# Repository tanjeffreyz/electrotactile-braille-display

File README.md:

<h1 align="center">Electrotactile Braille Display</h1> 

The Electrotactile Braille Display (ETBD) is a refreshable braille display that uses electrical pulses to simulate the feeling of braille dots on the user's fingertips. 
Because it has no moving parts, the ETBD has the potential to be much lighter, thinner, and cheaper compared to mechanical braille displays, which use physical braille pins.
 
<div align="center">
  
</div>
<br>
<div align="center">
  <a href="https://tanjeffreyz.github.io/electrotactile-braille-display"><b>Click here to view this project's full description</b></a>
</div>

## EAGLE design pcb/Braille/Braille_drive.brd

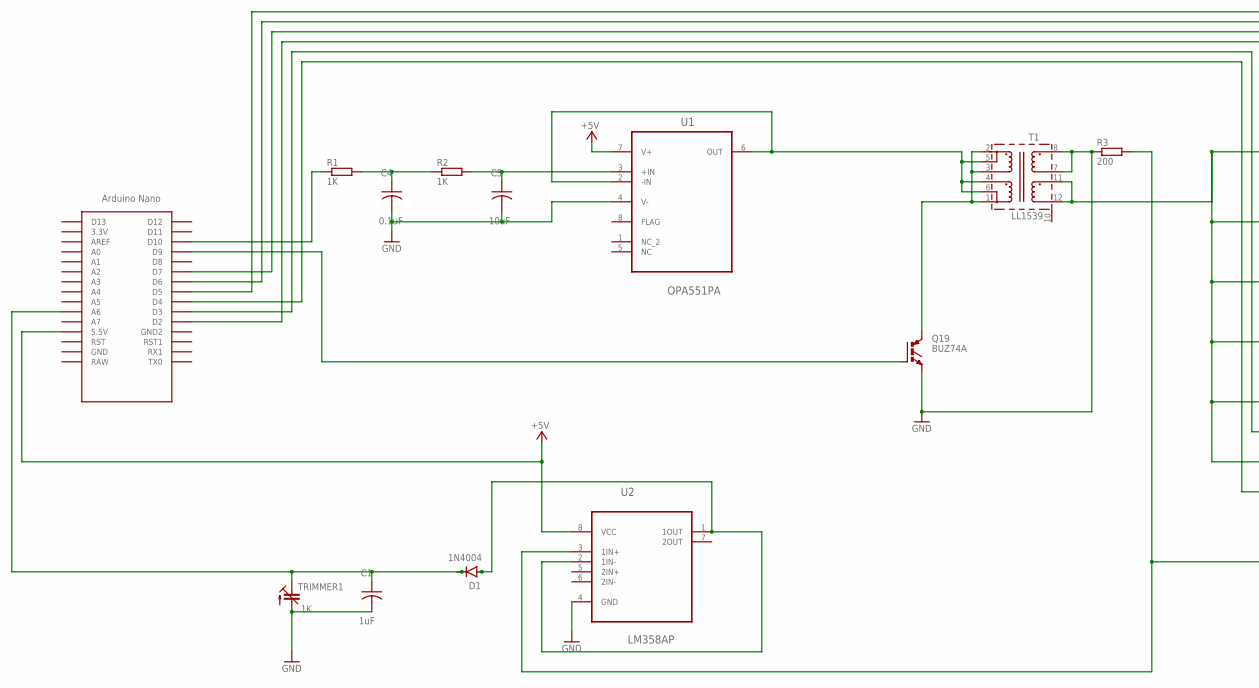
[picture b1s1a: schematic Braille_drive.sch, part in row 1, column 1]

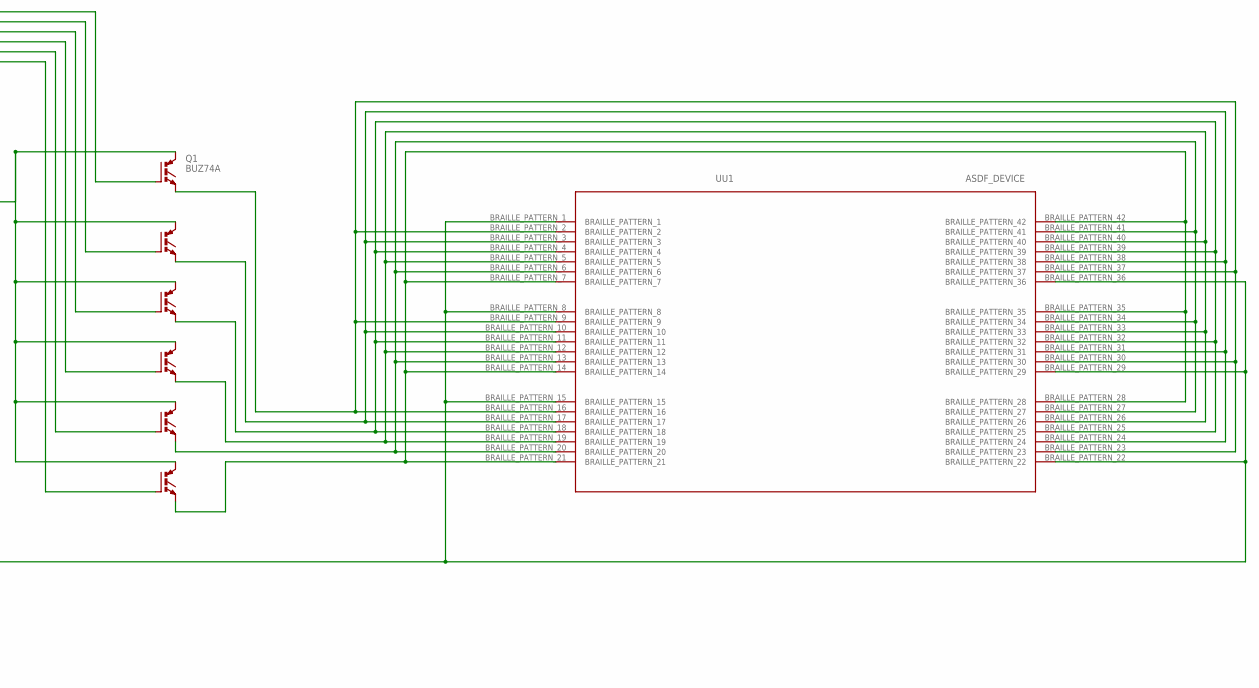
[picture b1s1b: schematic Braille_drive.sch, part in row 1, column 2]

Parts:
C1: 1uF; CAP_RADIAL_2MM
C4: 0.1uF; CAP_RADIAL_2MM
C5: 10uF; CAP_RADIAL_2MM
D1: 1N4004; DO-41
Q1, Q2, Q3, Q4, Q5, Q6, Q19: BUZ74A; TO220AV
R1, R2: 1K; 0204V
R3: 200; 0204V
T1: LL1539
TRIMMER1: 1K; CTRIM3040.452
U1: OPA551PA; DIP254P762X508-8
U2: LM358AP; DIP254P762X508-8
U$1: NANO
UU1: ASDF_DEVICE; BRAILLE_PATTERN1

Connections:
+5V: U1.7 (V+), U2.8 (VCC), U$1.5V (5.5V)
GND: C1.2, C4.2, C5.2, Q19.E, R3.1, T1.7, T1.8, TRIMMER1.2 (A), U1.4 (V-), U2.4 (GND)
unnamed: R1.1, U$1.D10
unnamed: C4.1, R1.2, R2.1
unnamed: C5.1, R2.2, U1.3 (+IN)
unnamed: T1.4, T1.5, T1.6, U1.2 (-IN), U1.6 (OUT)
unnamed: Q19.C, T1.1, T1.2, T1.3
unnamed: Q19.G, U$1.D9
unnamed: D1.A, U2.1 (1OUT), U2.2 (1IN-)
unnamed: C1.1, D1.C, TRIMMER1.1A (E), U$1.A6
unnamed: Q6.G, U$1.D4
unnamed: Q5.G, U$1.D3
unnamed: Q1.C, Q2.C, Q3.C, Q4.C, Q5.C, Q6.C, T1.11, T1.12
unnamed: Q4.G, U$1.D2
unnamed: Q6.E, UU1.BRAILLE_PATTERN_7, UU1.BRAILLE_PATTERN_14, UU1.BRAILLE_PATTERN_21, UU1.BRAILLE_PATTERN_28, UU1.BRAILLE_PATTERN_35, UU1.BRAILLE_PATTERN_42
unnamed: Q3.G, U$1.D7
unnamed: Q2.G, U$1.D6
unnamed: Q1.G, U$1.D5
unnamed: R3.2, U2.3 (1IN+), UU1.BRAILLE_PATTERN_1, UU1.BRAILLE_PATTERN_8, UU1.BRAILLE_PATTERN_15, UU1.BRAILLE_PATTERN_22, UU1.BRAILLE_PATTERN_29, UU1.BRAILLE_PATTERN_36
unnamed: Q5.E, UU1.BRAILLE_PATTERN_6, UU1.BRAILLE_PATTERN_13, UU1.BRAILLE_PATTERN_20, UU1.BRAILLE_PATTERN_27, UU1.BRAILLE_PATTERN_34, UU1.BRAILLE_PATTERN_41
unnamed: Q1.E, UU1.BRAILLE_PATTERN_2, UU1.BRAILLE_PATTERN_9, UU1.BRAILLE_PATTERN_16, UU1.BRAILLE_PATTERN_23, UU1.BRAILLE_PATTERN_30, UU1.BRAILLE_PATTERN_37
unnamed: Q4.E, UU1.BRAILLE_PATTERN_5, UU1.BRAILLE_PATTERN_12, UU1.BRAILLE_PATTERN_19, UU1.BRAILLE_PATTERN_26, UU1.BRAILLE_PATTERN_33, UU1.BRAILLE_PATTERN_40
unnamed: Q3.E, UU1.BRAILLE_PATTERN_4, UU1.BRAILLE_PATTERN_11, UU1.BRAILLE_PATTERN_18, UU1.BRAILLE_PATTERN_25, UU1.BRAILLE_PATTERN_32, UU1.BRAILLE_PATTERN_39
unnamed: Q2.E, UU1.BRAILLE_PATTERN_3, UU1.BRAILLE_PATTERN_10, UU1.BRAILLE_PATTERN_17, UU1.BRAILLE_PATTERN_24, UU1.BRAILLE_PATTERN_31, UU1.BRAILLE_PATTERN_38

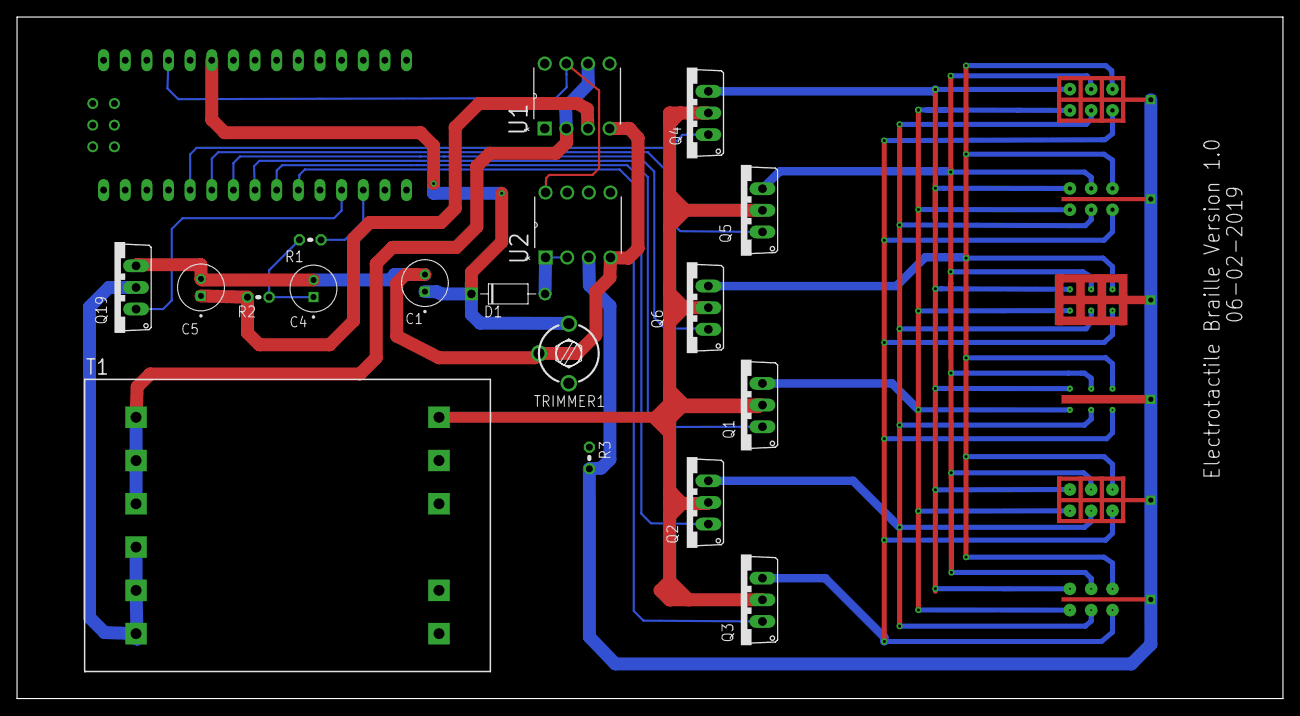
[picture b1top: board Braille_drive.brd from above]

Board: 2 copper layers, 148.6 x 80.0 mm, 20 parts (0 on the bottom side), 24 nets.

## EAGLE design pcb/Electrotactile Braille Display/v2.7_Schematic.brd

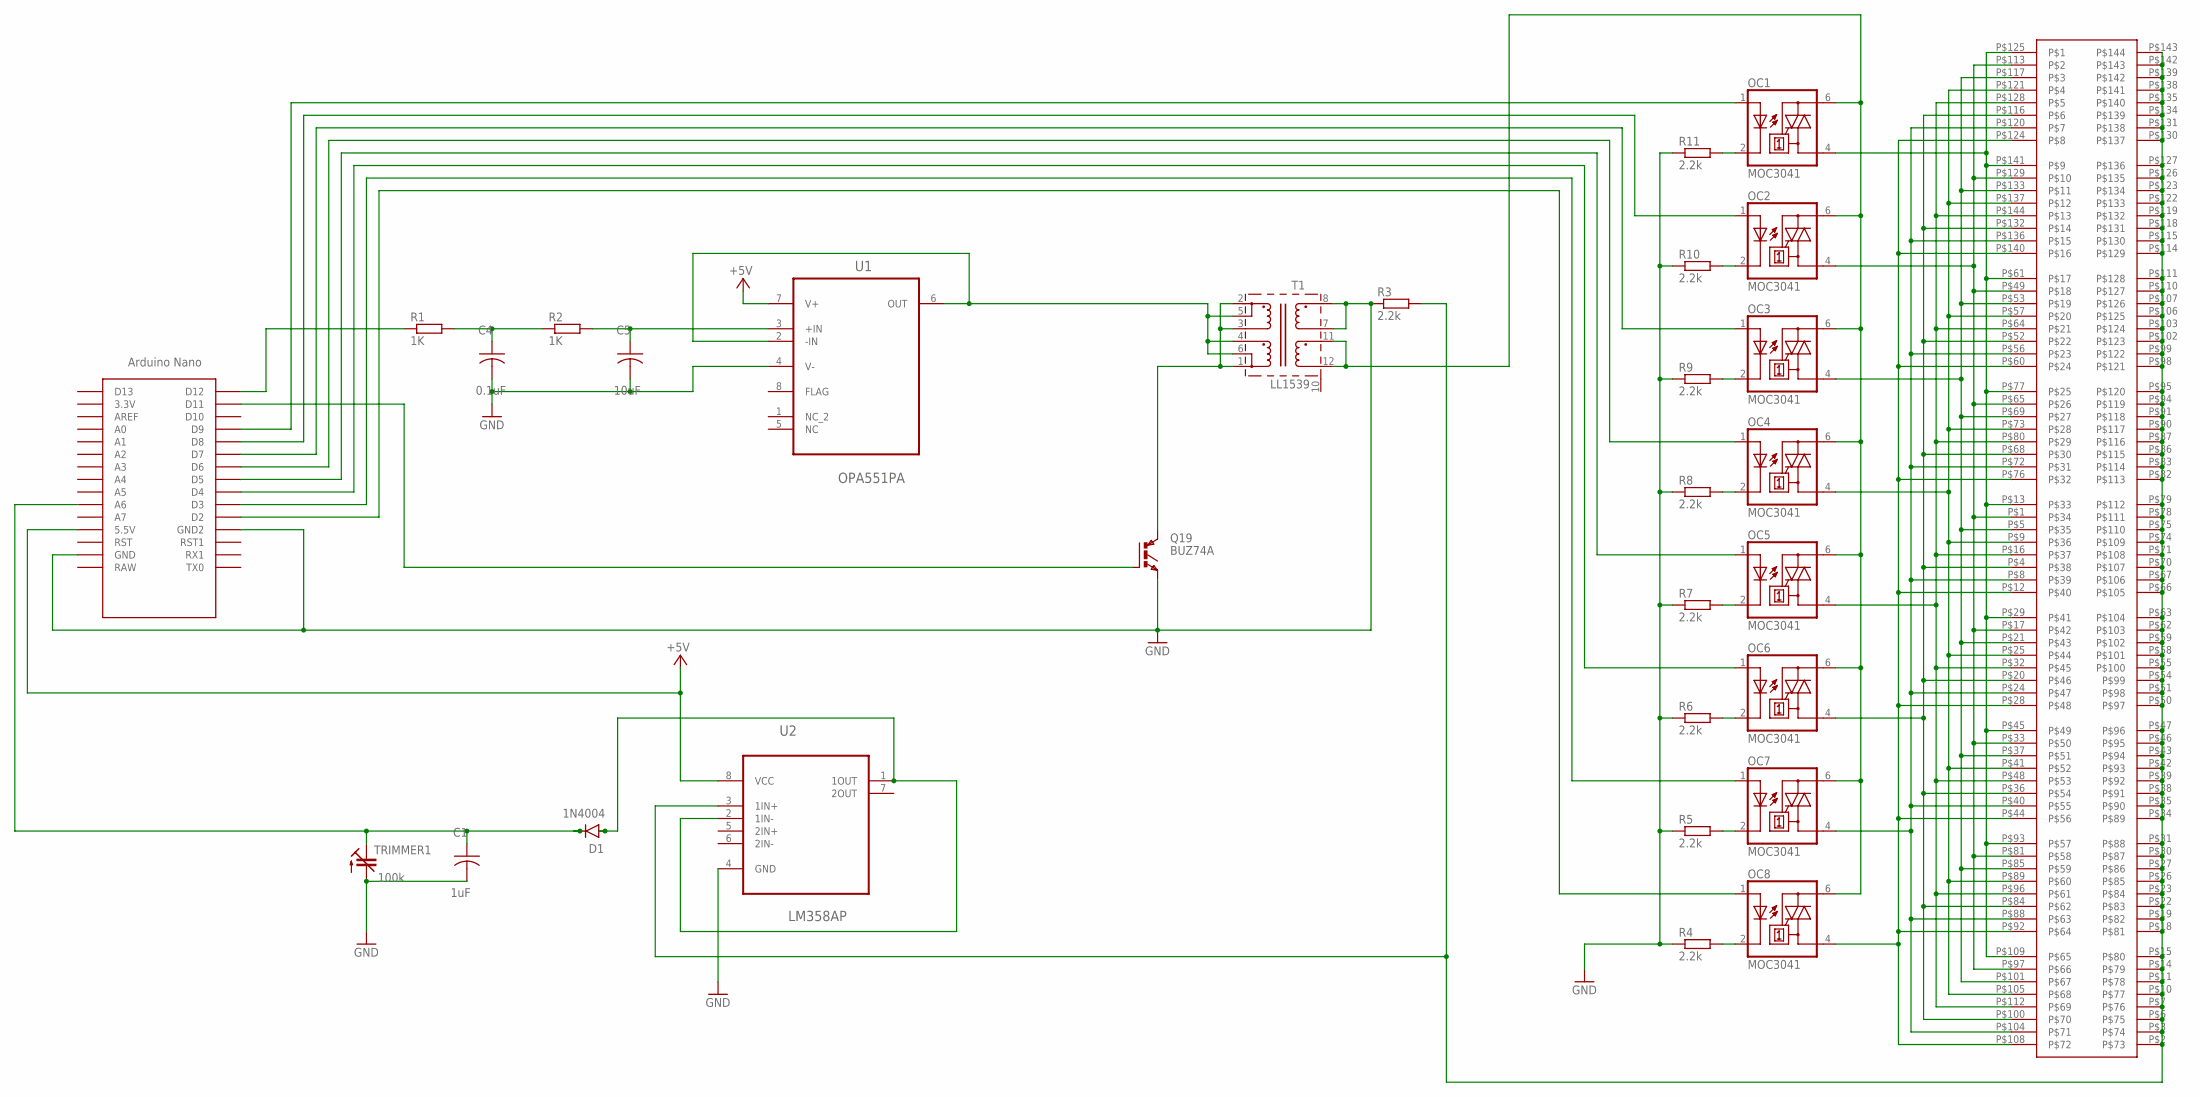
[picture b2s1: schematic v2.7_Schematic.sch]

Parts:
C1: 1uF; CAP_RADIAL_2MM
C4: 0.1uF; CAP_RADIAL_2MM
C5: 10uF; CAP_RADIAL_2MM
D1: 1N4004; DO-41
OC1, OC2, OC3, OC4, OC5, OC6, OC7, OC8: MOC3041; DIL06
Q19: BUZ74A; TO220AV
R1, R2: 1K; 0204V
R3, R4, R5, R6, R7, R8, R9, R10, R11: 2.2k; 0204V
T1: LL1539
TRIMMER1: 100k; CTRIM3040.452
U1: OPA551PA; DIP254P762X508-8
U2: LM358AP; DIP254P762X508-8
U$1: NANO
U$2: DOTS_V2

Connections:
+5V: U1.7 (V+), U2.8 (VCC), U$1.5V (5.5V)
GND: C1.2, C4.2, C5.2, Q19.E, R3.1, R4.1, R5.1, R6.1, R7.1, R8.1, R9.1, R10.1, R11.1, T1.7, T1.8, TRIMMER1.2 (A), U1.4 (V-), U2.4 (GND), U$1.GND, U$1.GND1 (GND2)
unnamed: OC7.2 (C), R5.2
unnamed: C4.1, R1.2, R2.1
unnamed: C5.1, R2.2, U1.3 (+IN)
unnamed: T1.4, T1.5, T1.6, U1.2 (-IN), U1.6 (OUT)
unnamed: Q19.C, T1.1, T1.2, T1.3
unnamed: Q19.G, U$1.D11
unnamed: D1.A, U2.1 (1OUT), U2.2 (1IN-)
unnamed: C1.1, D1.C, TRIMMER1.1A (E), U$1.A6
unnamed: OC8.1 (A), U$1.D2
unnamed: OC7.1 (A), U$1.D3
unnamed: OC2.1 (A), U$1.D8
unnamed: OC6.1 (A), U$1.D4
unnamed: R1.1, U$1.D12
unnamed: OC5.1 (A), U$1.D5
unnamed: OC4.1 (A), U$1.D6
unnamed: OC3.1 (A), U$1.D7
unnamed: R3.2, U2.3 (1IN+), U$2.P$2, U$2.P$3, U$2.P$6, U$2.P$7, U$2.P$10, U$2.P$11, U$2.P$14, U$2.P$15, U$2.P$18, U$2.P$19, U$2.P$22, U$2.P$23, U$2.P$26, U$2.P$27, U$2.P$30, U$2.P$31, U$2.P$34, U$2.P$35, U$2.P$38, U$2.P$39, U$2.P$42, U$2.P$43, U$2.P$46, U$2.P$47, U$2.P$50, U$2.P$51, U$2.P$54, U$2.P$55, U$2.P$58, U$2.P$59, U$2.P$62, U$2.P$63, U$2.P$66, U$2.P$67, U$2.P$70, U$2.P$71, U$2.P$74, U$2.P$75, U$2.P$78, U$2.P$79, U$2.P$82, U$2.P$83, U$2.P$86, U$2.P$87, U$2.P$90, U$2.P$91, U$2.P$94, U$2.P$95, U$2.P$98, U$2.P$99, U$2.P$102, U$2.P$103, U$2.P$106, U$2.P$107, U$2.P$110, U$2.P$111, U$2.P$114, U$2.P$115, U$2.P$118, U$2.P$119, U$2.P$122, U$2.P$123, U$2.P$126, U$2.P$127, U$2.P$130, U$2.P$131, U$2.P$134, U$2.P$135, U$2.P$138, U$2.P$139, U$2.P$142, U$2.P$143
unnamed: OC1.6 (A2), OC2.6 (A2), OC3.6 (A2), OC4.6 (A2), OC5.6 (A2), OC6.6 (A2), OC7.6 (A2), OC8.6 (A2), T1.11, T1.12
unnamed: OC4.4 (A1), U$2.P$9, U$2.P$25, U$2.P$41, U$2.P$57, U$2.P$73, U$2.P$89, U$2.P$105, U$2.P$121, U$2.P$137
unnamed: OC1.1 (A), U$1.D9
unnamed: OC2.4 (A1), U$2.P$1, U$2.P$17, U$2.P$33, U$2.P$49, U$2.P$65, U$2.P$81, U$2.P$97, U$2.P$113, U$2.P$129
unnamed: OC3.4 (A1), U$2.P$5, U$2.P$21, U$2.P$37, U$2.P$53, U$2.P$69, U$2.P$85, U$2.P$101, U$2.P$117, U$2.P$133
unnamed: OC5.4 (A1), U$2.P$16, U$2.P$32, U$2.P$48, U$2.P$64, U$2.P$80, U$2.P$96, U$2.P$112, U$2.P$128, U$2.P$144
unnamed: OC6.4 (A1), U$2.P$4, U$2.P$20, U$2.P$36, U$2.P$52, U$2.P$68, U$2.P$84, U$2.P$100, U$2.P$116, U$2.P$132
unnamed: OC7.4 (A1), U$2.P$8, U$2.P$24, U$2.P$40, U$2.P$56, U$2.P$72, U$2.P$88, U$2.P$104, U$2.P$120, U$2.P$136
unnamed: OC8.4 (A1), U$2.P$12, U$2.P$28, U$2.P$44, U$2.P$60, U$2.P$76, U$2.P$92, U$2.P$108, U$2.P$124, U$2.P$140
unnamed: OC8.2 (C), R4.2
unnamed: OC1.4 (A1), U$2.P$13, U$2.P$29, U$2.P$45, U$2.P$61, U$2.P$77, U$2.P$93, U$2.P$109, U$2.P$125, U$2.P$141
unnamed: OC6.2 (C), R6.2
unnamed: OC5.2 (C), R7.2
unnamed: OC4.2 (C), R8.2
unnamed: OC3.2 (C), R9.2
unnamed: OC2.2 (C), R10.2
unnamed: OC1.2 (C), R11.2

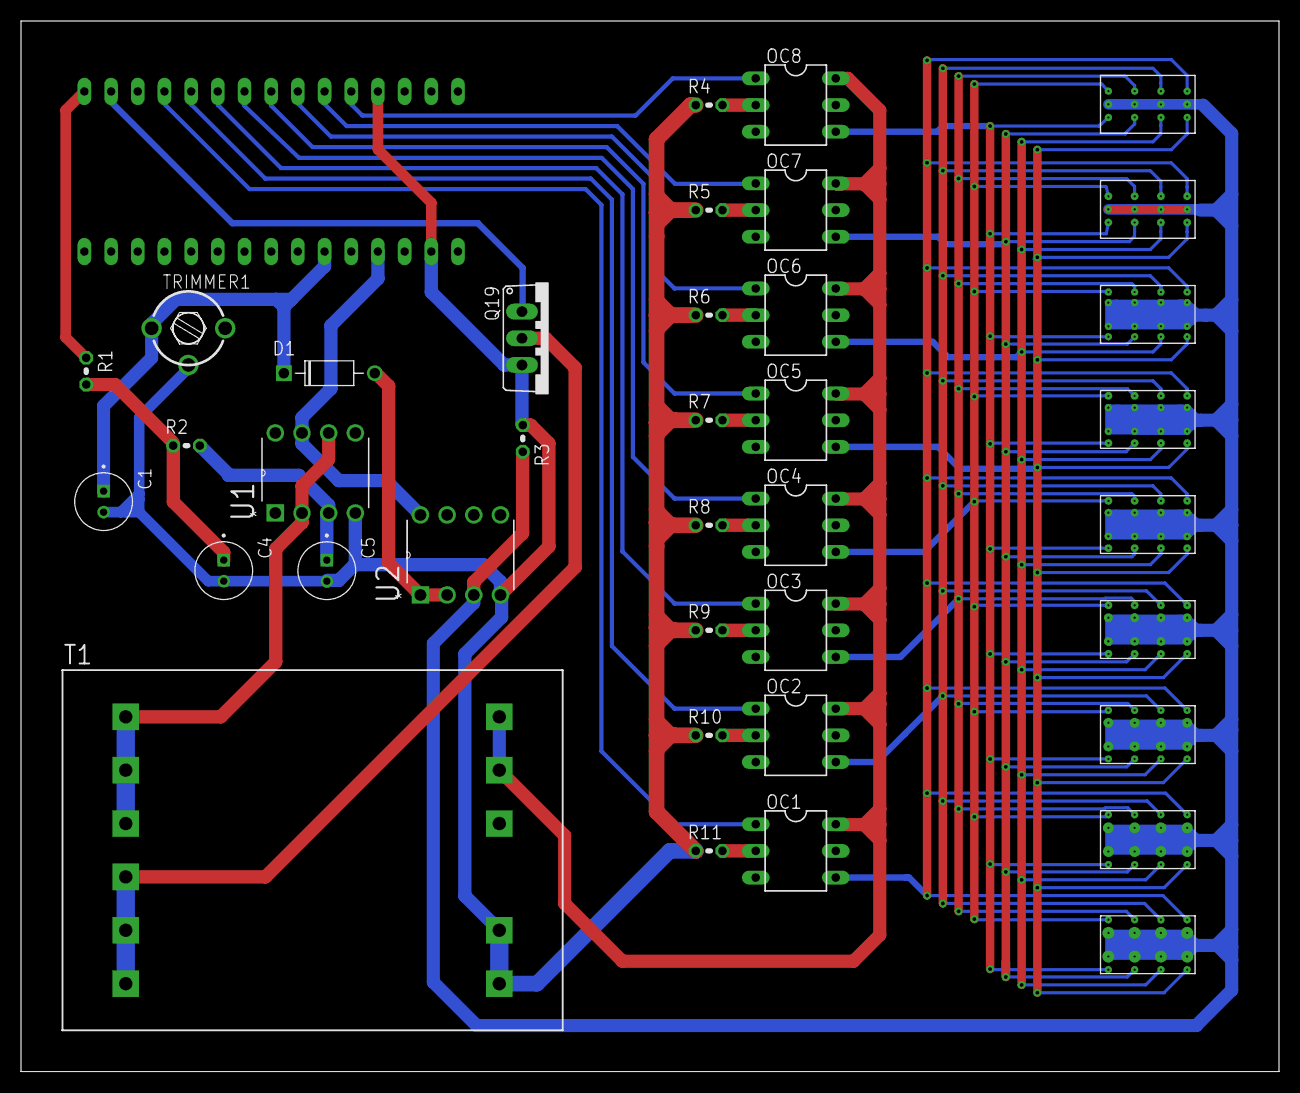
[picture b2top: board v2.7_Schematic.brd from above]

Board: 2 copper layers, 119.8 x 100.0 mm, 30 parts (0 on the bottom side), 36 nets.

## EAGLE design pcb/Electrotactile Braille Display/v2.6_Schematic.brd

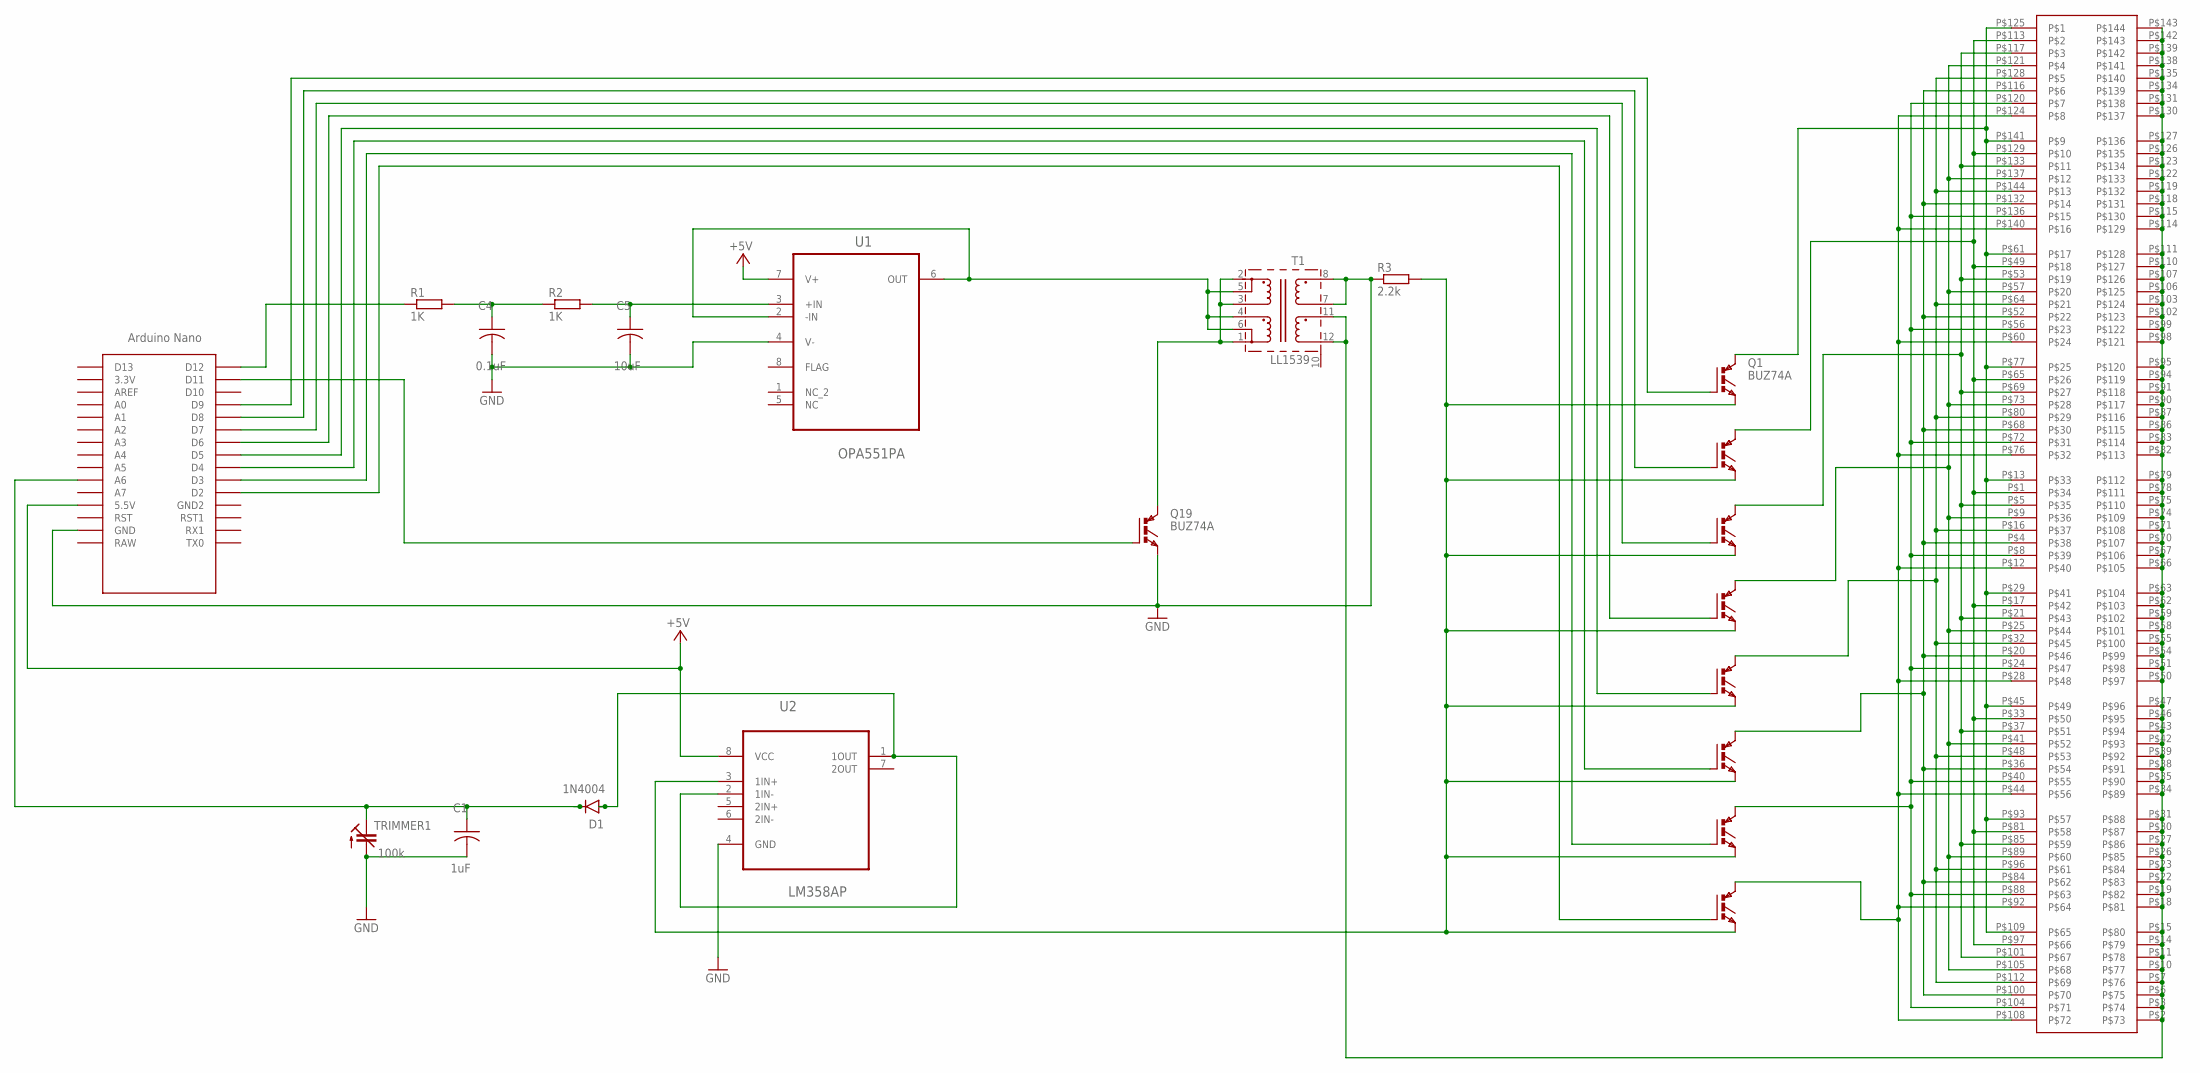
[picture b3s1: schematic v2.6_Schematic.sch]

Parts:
C1: 1uF; CAP_RADIAL_2MM
C4: 0.1uF; CAP_RADIAL_2MM
C5: 10uF; CAP_RADIAL_2MM
D1: 1N4004; DO-41
Q1, Q2, Q3, Q4, Q5, Q6, Q7, Q8, Q19: BUZ74A; TO220AV
R1, R2: 1K; 0204V
R3: 2.2k; 0204V
T1: LL1539
TRIMMER1: 100k; CTRIM3040.452
U1: OPA551PA; DIP254P762X508-8
U2: LM358AP; DIP254P762X508-8
U$1: NANO
U$2: DOTS_V2

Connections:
+5V: U1.7 (V+), U2.8 (VCC), U$1.5V (5.5V)
GND: C1.2, C4.2, C5.2, Q19.E, R3.1, T1.7, T1.8, TRIMMER1.2 (A), U1.4 (V-), U2.4 (GND), U$1.GND
unnamed: T1.11, T1.12, U$2.P$2, U$2.P$3, U$2.P$6, U$2.P$7, U$2.P$10, U$2.P$11, U$2.P$14, U$2.P$15, U$2.P$18, U$2.P$19, U$2.P$22, U$2.P$23, U$2.P$26, U$2.P$27, U$2.P$30, U$2.P$31, U$2.P$34, U$2.P$35, U$2.P$38, U$2.P$39, U$2.P$42, U$2.P$43, U$2.P$46, U$2.P$47, U$2.P$50, U$2.P$51, U$2.P$54, U$2.P$55, U$2.P$58, U$2.P$59, U$2.P$62, U$2.P$63, U$2.P$66, U$2.P$67, U$2.P$70, U$2.P$71, U$2.P$74, U$2.P$75, U$2.P$78, U$2.P$79, U$2.P$82, U$2.P$83, U$2.P$86, U$2.P$87, U$2.P$90, U$2.P$91, U$2.P$94, U$2.P$95, U$2.P$98, U$2.P$99, U$2.P$102, U$2.P$103, U$2.P$106, U$2.P$107, U$2.P$110, U$2.P$111, U$2.P$114, U$2.P$115, U$2.P$118, U$2.P$119, U$2.P$122, U$2.P$123, U$2.P$126, U$2.P$127, U$2.P$130, U$2.P$131, U$2.P$134, U$2.P$135, U$2.P$138, U$2.P$139, U$2.P$142, U$2.P$143
unnamed: C4.1, R1.2, R2.1
unnamed: C5.1, R2.2, U1.3 (+IN)
unnamed: T1.4, T1.5, T1.6, U1.2 (-IN), U1.6 (OUT)
unnamed: Q19.C, T1.1, T1.2, T1.3
unnamed: Q19.G, U$1.D11
unnamed: D1.A, U2.1 (1OUT), U2.2 (1IN-)
unnamed: C1.1, D1.C, TRIMMER1.1A (E), U$1.A6
unnamed: Q8.G, U$1.D2
unnamed: Q7.G, U$1.D3
unnamed: Q2.G, U$1.D8
unnamed: Q6.G, U$1.D4
unnamed: R1.1, U$1.D12
unnamed: Q5.G, U$1.D5
unnamed: Q4.G, U$1.D6
unnamed: Q3.G, U$1.D7
unnamed: Q1.E, Q2.E, Q3.E, Q4.E, Q5.E, Q6.E, Q7.E, Q8.E, R3.2, U2.3 (1IN+)
unnamed: Q4.C, U$2.P$9, U$2.P$25, U$2.P$41, U$2.P$57, U$2.P$73, U$2.P$89, U$2.P$105, U$2.P$121, U$2.P$137
unnamed: Q1.G, U$1.D9
unnamed: Q2.C, U$2.P$1, U$2.P$17, U$2.P$33, U$2.P$49, U$2.P$65, U$2.P$81, U$2.P$97, U$2.P$113, U$2.P$129
unnamed: Q3.C, U$2.P$5, U$2.P$21, U$2.P$37, U$2.P$53, U$2.P$69, U$2.P$85, U$2.P$101, U$2.P$117, U$2.P$133
unnamed: Q5.C, U$2.P$16, U$2.P$32, U$2.P$48, U$2.P$64, U$2.P$80, U$2.P$96, U$2.P$112, U$2.P$128, U$2.P$144
unnamed: Q6.C, U$2.P$4, U$2.P$20, U$2.P$36, U$2.P$52, U$2.P$68, U$2.P$84, U$2.P$100, U$2.P$116, U$2.P$132
unnamed: Q7.C, U$2.P$8, U$2.P$24, U$2.P$40, U$2.P$56, U$2.P$72, U$2.P$88, U$2.P$104, U$2.P$120, U$2.P$136
unnamed: Q8.C, U$2.P$12, U$2.P$28, U$2.P$44, U$2.P$60, U$2.P$76, U$2.P$92, U$2.P$108, U$2.P$124, U$2.P$140
unnamed: Q1.C, U$2.P$13, U$2.P$29, U$2.P$45, U$2.P$61, U$2.P$77, U$2.P$93, U$2.P$109, U$2.P$125, U$2.P$141

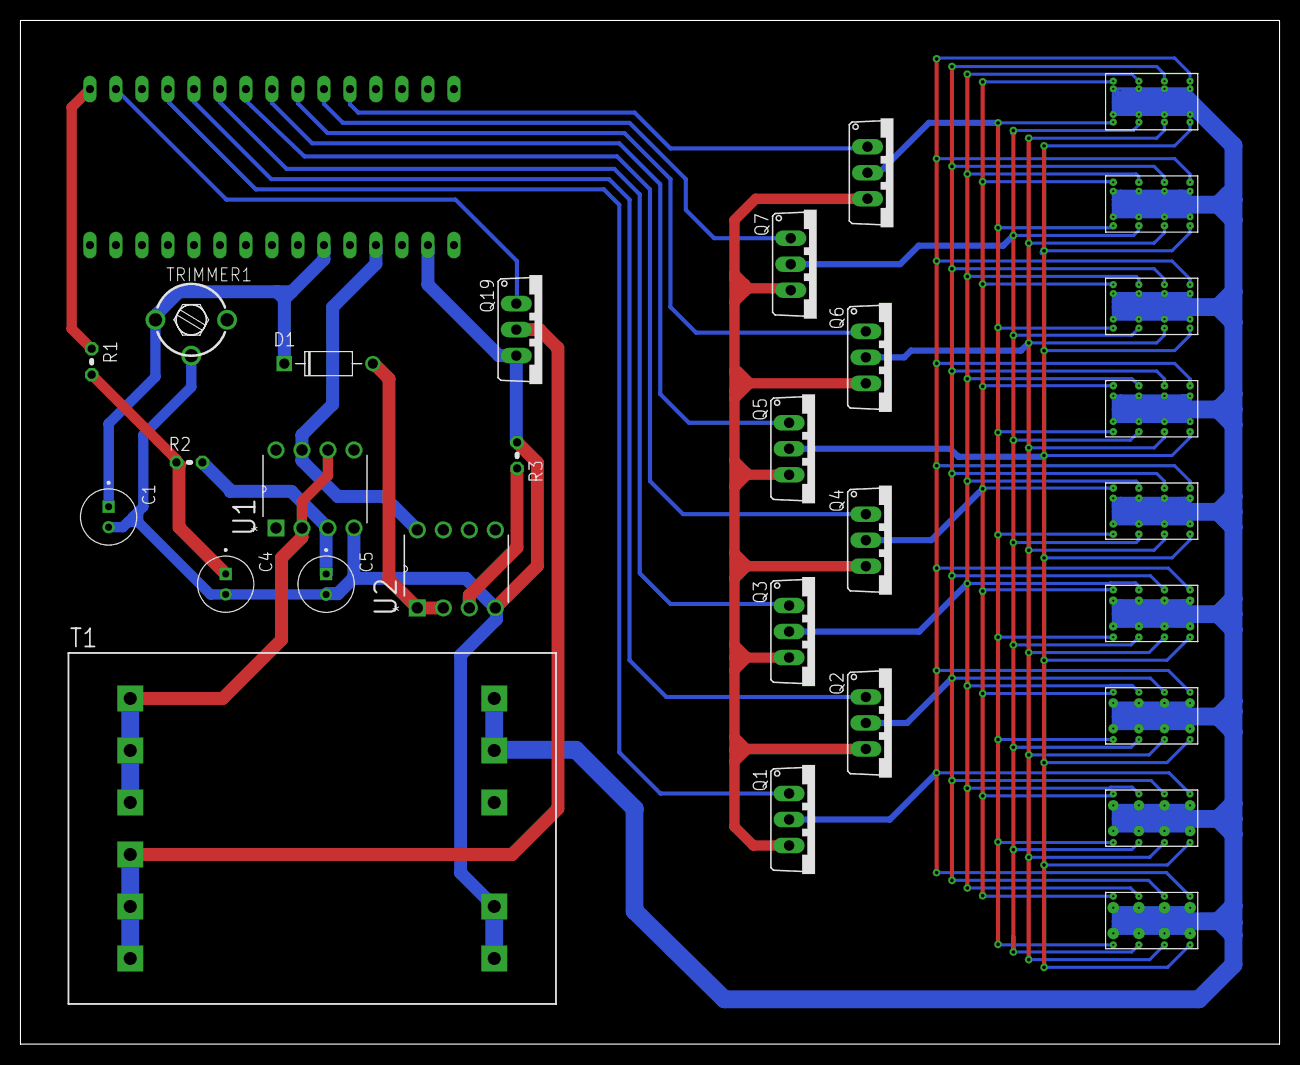
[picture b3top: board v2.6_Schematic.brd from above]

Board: 2 copper layers, 123.0 x 100.0 mm, 22 parts (0 on the bottom side), 28 nets.

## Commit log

2021-07-29 uploaded etbd
2021-07-29 uploaded some images
2021-07-29 fixed some naming conventions
2021-07-29 renamed
2021-07-29 reverted, should update name now
2022-05-18 removed everything, ready to start on website
2022-05-19 finished webpage for etbd
2022-05-19 added favicon
2022-05-19 added redirects to github
2022-05-19 fixed file name causing versions 2 and 3 not rendering
2022-05-19 increased border radius of pictures
2022-05-20 added keywords to webpage
2022-05-21 fixed quotation error
